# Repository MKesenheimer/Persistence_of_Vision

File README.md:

# Persistence_of_Vision
A simple circuit to project text messages into the air with the help of a camera

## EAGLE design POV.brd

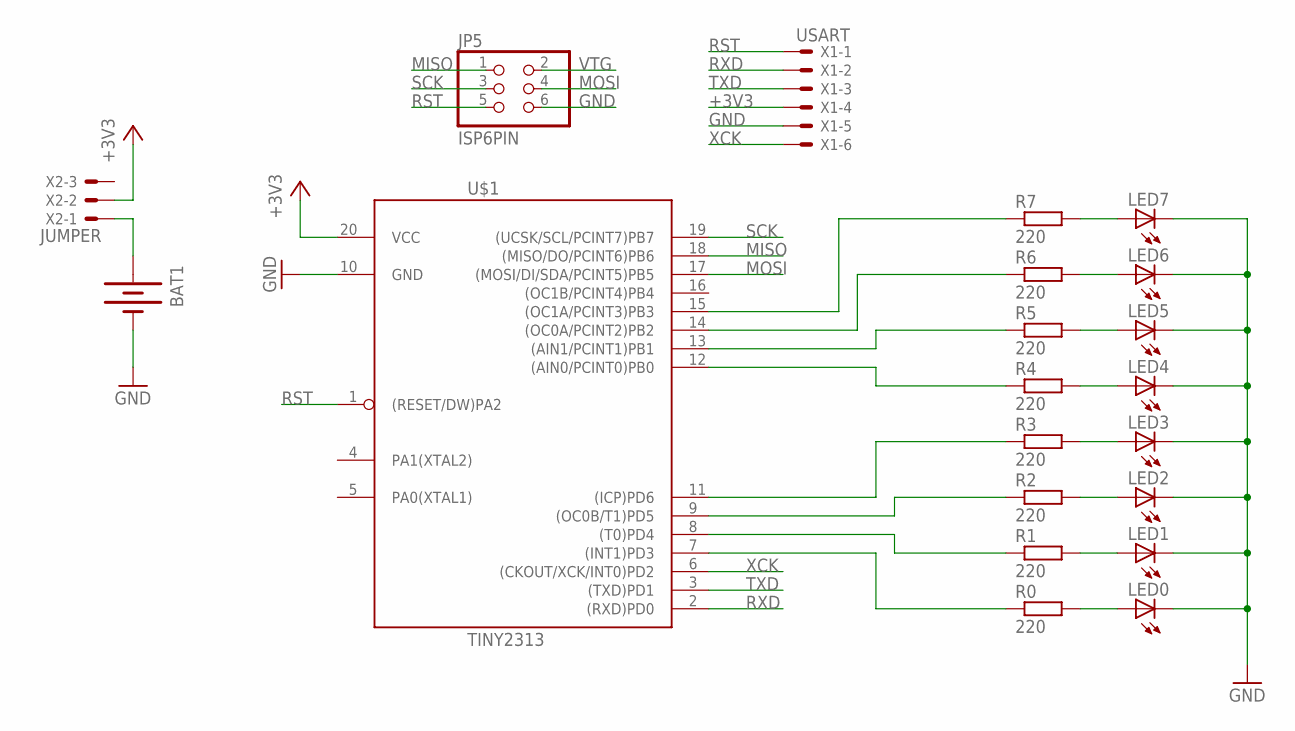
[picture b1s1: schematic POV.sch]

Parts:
BAT1: BATTERY20PTH; BATTCOM_20MM_PTH
JP5: ISP6PIN; 2X03
LED0, LED1, LED2, LED3, LED4, LED5, LED6, LED7: LED3MM
R0, R1, R2, R3, R4, R5, R6, R7: 220; 0207/10
U$1: TINY2313; DIL20
X1: USART; 22-23-2061
X2: JUMPER; 22-23-2031

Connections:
+3V3: U$1.20 (VCC), X1.4, X2.2
GND: BAT1.2 (-), JP5.6, LED0.K (C), LED1.K (C), LED2.K (C), LED3.K (C), LED4.K (C), LED5.K (C), LED6.K (C), LED7.K (C), U$1.10 (GND), X1.5
MISO: JP5.1, U$1.18 ((MISO/DO/PCINT6)PB6)
MOSI: JP5.4, U$1.17 ((MOSI/DI/SDA/PCINT5)PB5)
unnamed: R0.1, U$1.7 ((INT1)PD3)
unnamed: R1.1, U$1.8 ((T0)PD4)
unnamed: R2.1, U$1.9 ((OC0B/T1)PD5)
unnamed: R3.1, U$1.11 ((ICP)PD6)
unnamed: R4.1, U$1.12 ((AIN0/PCINT0)PB0)
unnamed: R5.1, U$1.13 ((AIN1/PCINT1)PB1)
unnamed: R6.1, U$1.14 ((OC0A/PCINT2)PB2)
unnamed: R7.1, U$1.15 ((OC1A/PCINT3)PB3)
unnamed: LED7.A, R7.2
unnamed: LED6.A, R6.2
unnamed: LED5.A, R5.2
unnamed: LED4.A, R4.2
unnamed: LED3.A, R3.2
unnamed: LED2.A, R2.2
unnamed: LED1.A, R1.2
unnamed: LED0.A, R0.2
unnamed: BAT1.1 (+), X2.1
RST: JP5.5, U$1.1 ((RESET/DW)PA2), X1.1
RXD: U$1.2 ((RXD)PD0), X1.2
SCK: JP5.3, U$1.19 ((UCSK/SCL/PCINT7)PB7)
TXD: U$1.3 ((TXD)PD1), X1.3
VTG: JP5.2
XCK: U$1.6 ((CKOUT/XCK/INT0)PD2), X1.6

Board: 2 copper layers, 21 parts (0 on the bottom side), 26 nets, no tracks yet.

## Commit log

2015-10-03 Bilder aussortiert
2015-10-04 Schaltplan hinzugefügt

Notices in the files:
parts and their libraries:
SparkFun-Electromechanical: Licensing: Creative Commons ShareAlike 4.0 International - https://creativecommons.org/licenses/by-sa/4.0
